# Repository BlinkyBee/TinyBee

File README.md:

#TinyBee

Basic circuit for controlling a strip of 3 wire LEDs. Assumes external regulated 5V and is housed in a [polycase FB-30](http://www.polycase.com/fb-301) enclosure.

Uses micronucleus bootloader.

V1 is attiny85
V2 is attiny167

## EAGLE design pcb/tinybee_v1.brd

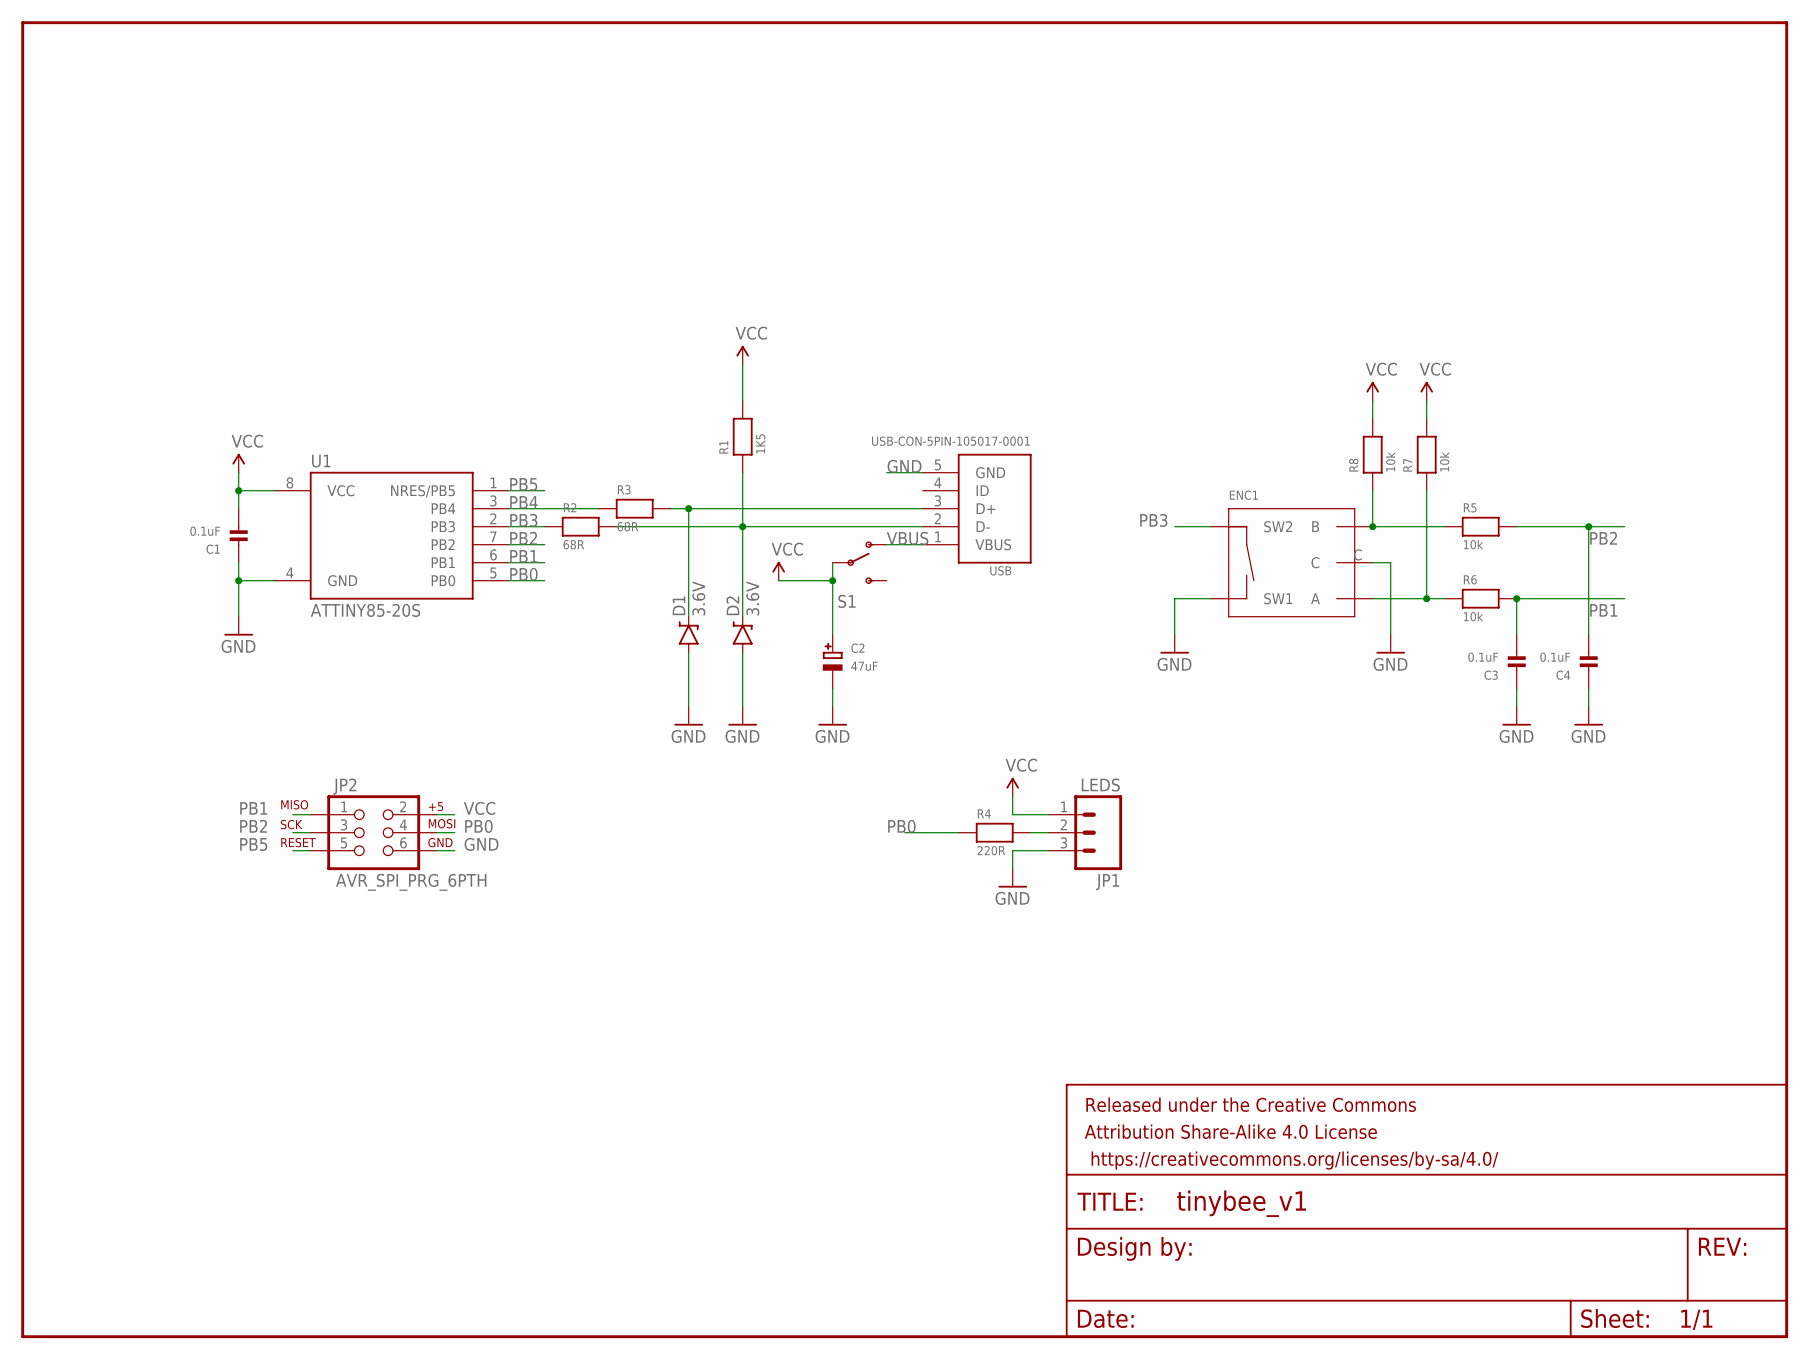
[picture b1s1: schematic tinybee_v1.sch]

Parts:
C1, C3, C4: 0.1uF; 0603
C2: 47uF; PANASONIC_C
D1, D2: 3.6V; SOD-323
ENC1: ROTARY-ENCODER-PEC12R
FRAME1: FRAME-LETTER; CREATIVE_COMMONS
JP1: LEDS; 1X03
JP2: AVR_SPI_PRG_6PTH; 2X3
R1: 1K5; 0603
R2, R3: 68R; 0603
R4: 220R; 0603
R5, R6, R7, R8: 10k; 0603
S1: SWITCH-SLIDE-SPDT-RIGHTANGLE-500; SWITCH-SPDT-RIGHTANGLE-500
U1: ATTINY85-20S; SOIC8_EIAJ_208MIL
USB: USB-CON-5PIN-105017-0001; USB-MICRO-MOLEX-105017-0001

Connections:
GND: C1.1, C2.-, C3.1, C4.1, D1.A, D2.A, ENC1.C, ENC1.SW1, JP1.3, JP2.6, U1.4 (GND), USB.5 (GND)
unnamed: D2.C, R1.1, R2.2, USB.2 (D-)
unnamed: D1.C, R3.2, USB.3 (D+)
unnamed: ENC1.A, R6.1, R7.1
unnamed: ENC1.B, R5.1, R8.1
unnamed: JP1.2, R4.2
PB0: JP2.4, R4.1, U1.5 (PB0)
PB1: C3.2, JP2.1, R6.2, U1.6 (PB1)
PB2: C4.2, JP2.3, R5.2, U1.7 (PB2)
PB3: ENC1.SW2, R2.1, U1.2 (PB3)
PB4: R3.1, U1.3 (PB4)
PB5: JP2.5, U1.1 (NRES/PB5)
VBUS: S1.SW1 (1), USB.1 (VBUS)
VCC: C1.2, C2.+, JP1.1, JP2.2, R1.2, R7.2, R8.2, S1.SWC (COMMON), U1.8 (VCC)

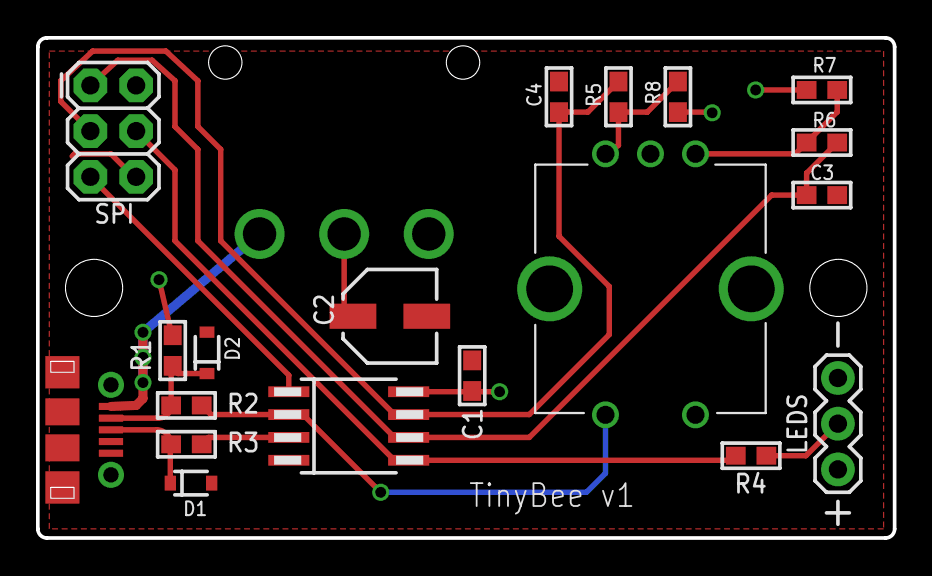
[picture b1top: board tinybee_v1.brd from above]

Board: 2 copper layers, 47.6 x 27.8 mm, 22 parts (0 on the bottom side), 14 nets.

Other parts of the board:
U$1: FB-30

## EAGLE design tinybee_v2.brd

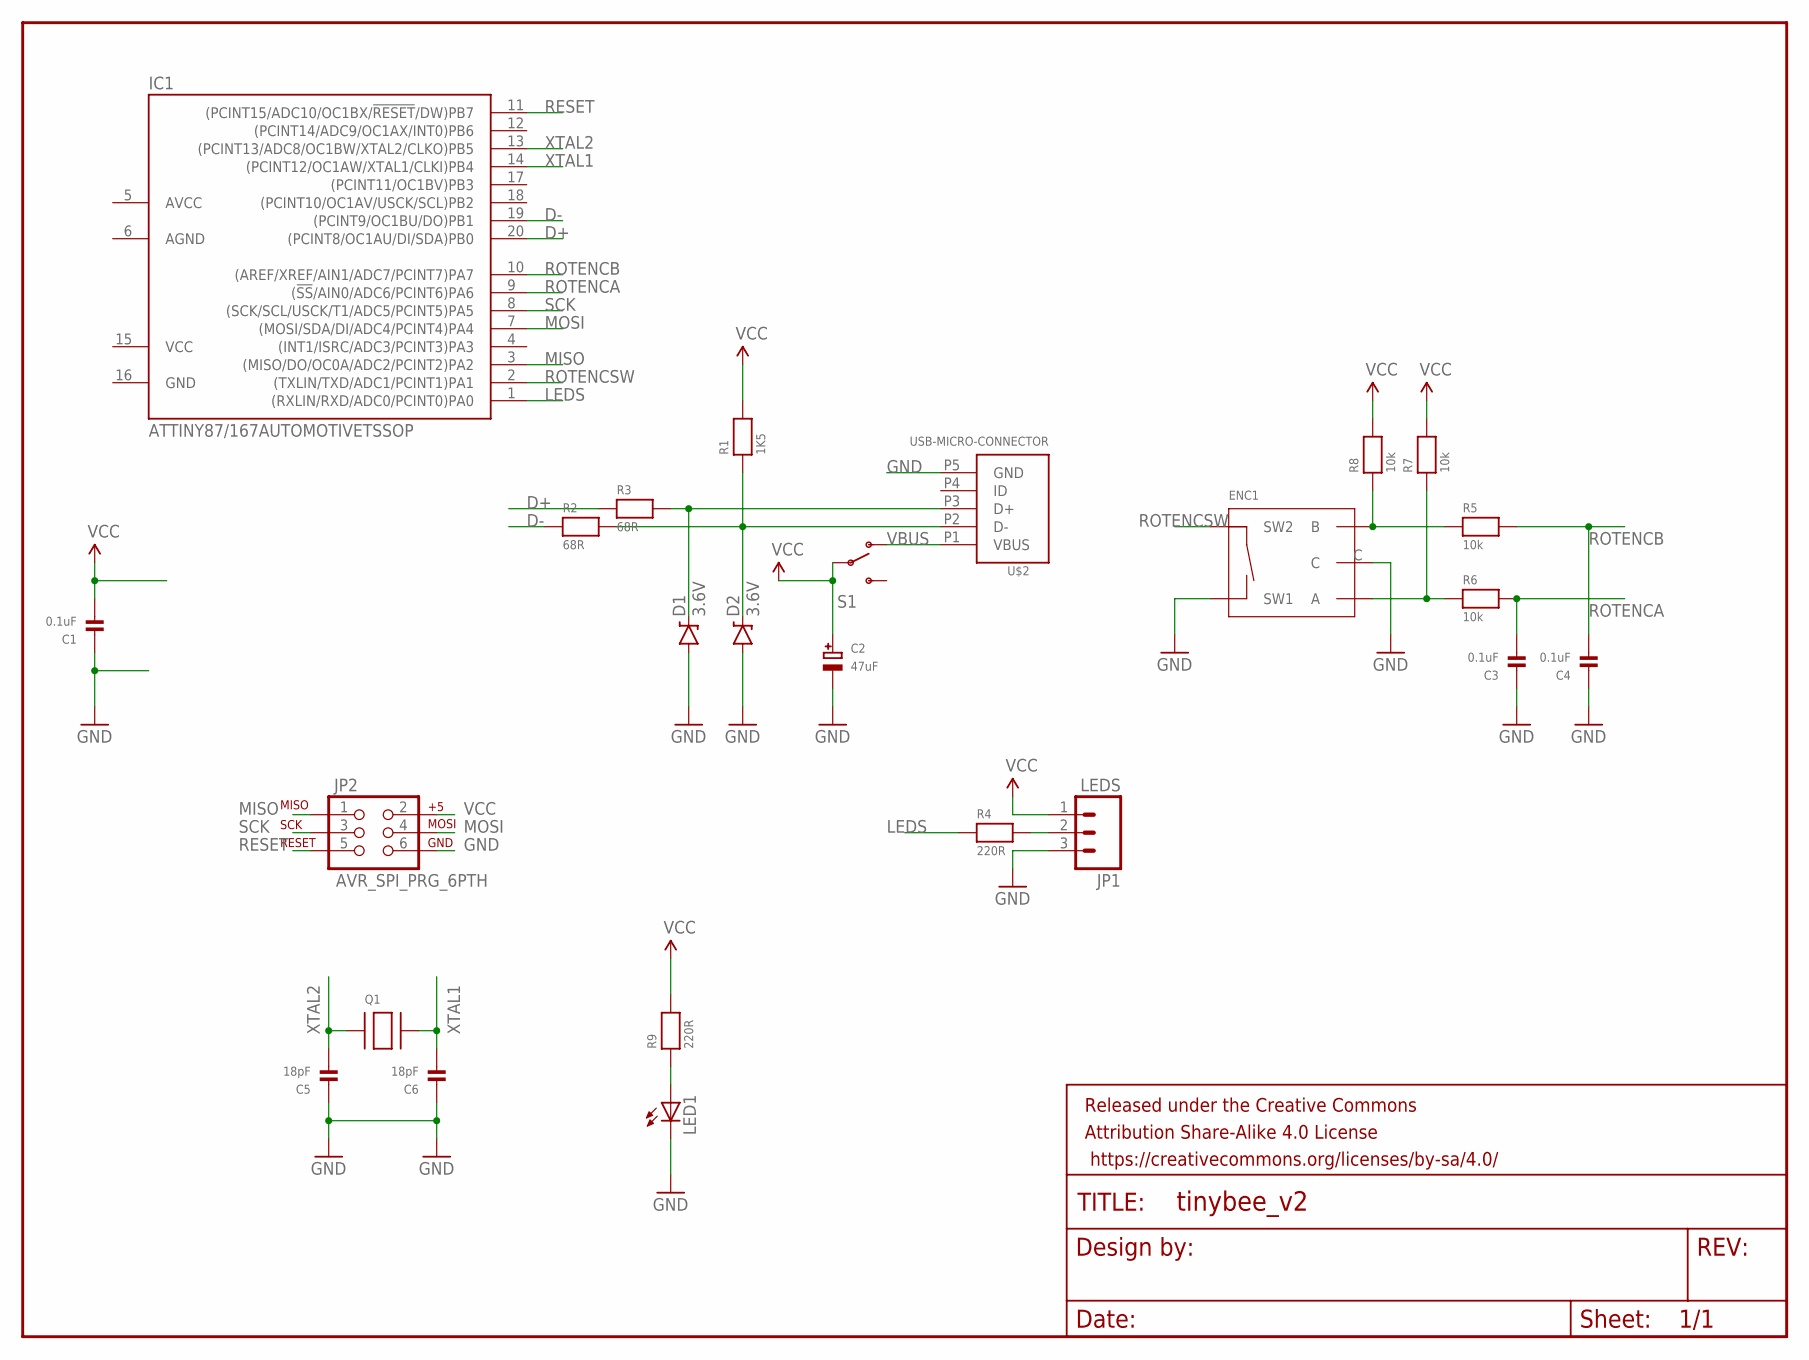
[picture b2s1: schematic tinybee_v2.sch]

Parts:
C1, C3, C4: 0.1uF; 0603
C2: 47uF; PANASONIC_C
C5, C6: 18pF; 0603
D1, D2: 3.6V; SOD-323
ENC1: ROTARY-ENCODER-PEC12R
FRAME1: FRAME-LETTER; CREATIVE_COMMONS
IC1: ATTINY87/167AUTOMOTIVETSSOP; TSSOP20
JP1: LEDS; 1X03
JP2: AVR_SPI_PRG_6PTH; 2X3
LED1: LEDCHIPLED_0603; CHIPLED_0603
Q1: CRYSTAL; ABLS7M2
R1: 1K5; 0603
R2, R3: 68R; 0603
R4, R9: 220R; 0603
R5, R6, R7, R8: 10k; 0603
S1: SWITCH-SLIDE-SPDT-RIGHTANGLE-500; SWITCH-SPDT-RIGHTANGLE-500
U$2: USB-MICRO-CONNECTOR; DX4R005JJ6/7

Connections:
D+: IC1.20 ((PCINT8/OC1AU/DI/SDA)PB0), R3.1
D-: IC1.19 ((PCINT9/OC1BU/DO)PB1), R2.1
GND: C1.1, C2.-, C3.1, C4.1, C5.1, C6.1, D1.A, D2.A, ENC1.C, ENC1.SW1, IC1.16 (GND), JP1.3, JP2.6, LED1.C, U$2.P5 (GND)
LEDS: IC1.1 ((RXLIN/RXD/ADC0/PCINT0)PA0), R4.1
MISO: IC1.3 ((MISO/DO/OC0A/ADC2/PCINT2)PA2), JP2.1
MOSI: IC1.7 ((MOSI/SDA/DI/ADC4/PCINT4)PA4), JP2.4
unnamed: D2.C, R1.1, R2.2, U$2.P2 (D-)
unnamed: D1.C, R3.2, U$2.P3 (D+)
unnamed: ENC1.A, R6.1, R7.1
unnamed: LED1.A, R9.1
unnamed: ENC1.B, R5.1, R8.1
unnamed: JP1.2, R4.2
RESET: IC1.11 ((PCINT15/ADC10/OC1BX/!RESET!/DW)PB7), JP2.5
ROTENCA: C3.2, IC1.9 ((!SS!/AIN0/ADC6/PCINT6)PA6), R6.2
ROTENCB: C4.2, IC1.10 ((AREF/XREF/AIN1/ADC7/PCINT7)PA7), R5.2
ROTENCSW: ENC1.SW2, IC1.2 ((TXLIN/TXD/ADC1/PCINT1)PA1)
SCK: IC1.8 ((SCK/SCL/USCK/T1/ADC5/PCINT5)PA5), JP2.3
VBUS: S1.SW1 (1), U$2.P1 (VBUS)
VCC: C1.2, C2.+, IC1.15 (VCC), JP1.1, JP2.2, R1.2, R7.2, R8.2, R9.2, S1.SWC (COMMON)
XTAL1: C6.2, IC1.14 ((PCINT12/OC1AW/XTAL1/CLKI)PB4), Q1.P$2
XTAL2: C5.2, IC1.13 ((PCINT13/ADC8/OC1BW/XTAL2/CLKO)PB5), Q1.P$1

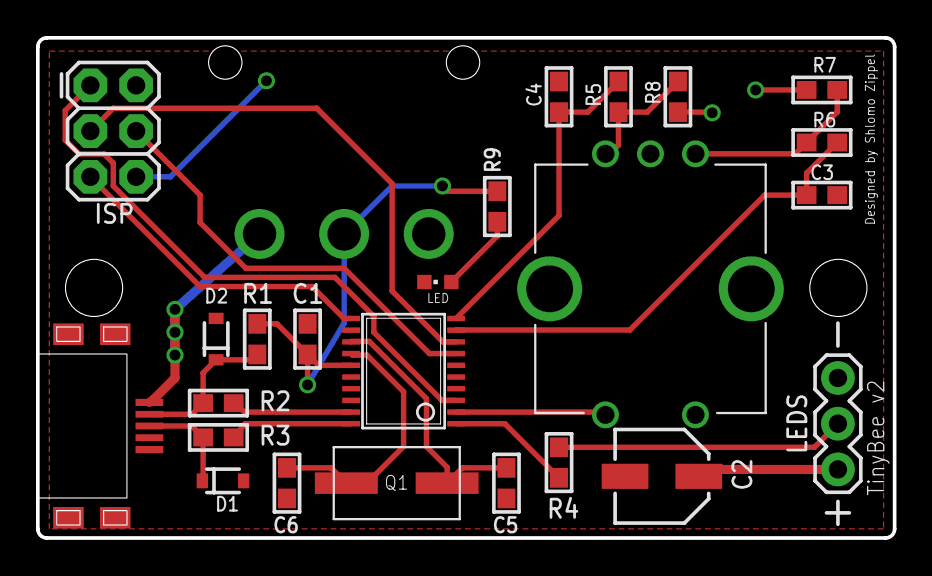
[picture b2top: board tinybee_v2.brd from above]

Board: 2 copper layers, 47.6 x 27.8 mm, 27 parts (0 on the bottom side), 21 nets.

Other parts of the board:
U$1: FB-30

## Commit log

2015-06-17 Added gitignore
2015-06-17 Schematic and board. No routing yet
2015-06-17 Fixes after Eran review
2015-06-17 moved a few pieces
2015-06-18 route
2015-06-20 routing
2015-06-24 Final touches. Redid USB connector footprint
2015-06-24 More cleanup
2015-06-24 final version of USB connector. removed names
2015-08-01 minor touchup
2015-08-15 Added initial arduino code
2015-08-15 readme
2015-08-20 Added rotenc switch, using a few patterns from fastled demoreel
2015-08-25 Added auto cycle, fading
2015-08-25 Save and restore state to EEPROM
2015-08-26 Production

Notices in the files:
parts and their libraries:
microbuilder: This work is placed in the public domain, and may be freely used for commercial and non-commercial work with the following conditions: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
SparkFun-DiscreteSemi: Licensing: Creative Commons ShareAlike 4.0 International - https://creativecommons.org/licenses/by-sa/4.0
